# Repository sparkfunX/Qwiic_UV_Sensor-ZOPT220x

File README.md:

Qwiic UV Sensor - ZZOPT2201
========================================

[*SPX-14264*](https://www.sparkfun.com/products/14264)

The ZOPT2201 is an excellent UVBS (ultraviolet energy sensor) in that it does true 310nm UVB sensing, not interpolated UV from ambient light like most sensors on the market. Without fuss or weird look up tables this sensor gives the current UV Index accurately.

The [Qwiic system](http://www.sparkfun.com/qwiic) enables fast and solderless connection between popular platforms and various sensors and actuators. You can read more about the Qwiic system [here](http://www.sparkfun.com/qwiic). 

License Information
-------------------

This product is _**open source**_!

Please review the LICENSE.md file for license information.

If you have any questions or concerns on licensing, please contact techsupport@sparkfun.com.

Distributed as-is; no warranty is given.

- Your friends at SparkFun.

_<COLLABORATION CREDIT>_

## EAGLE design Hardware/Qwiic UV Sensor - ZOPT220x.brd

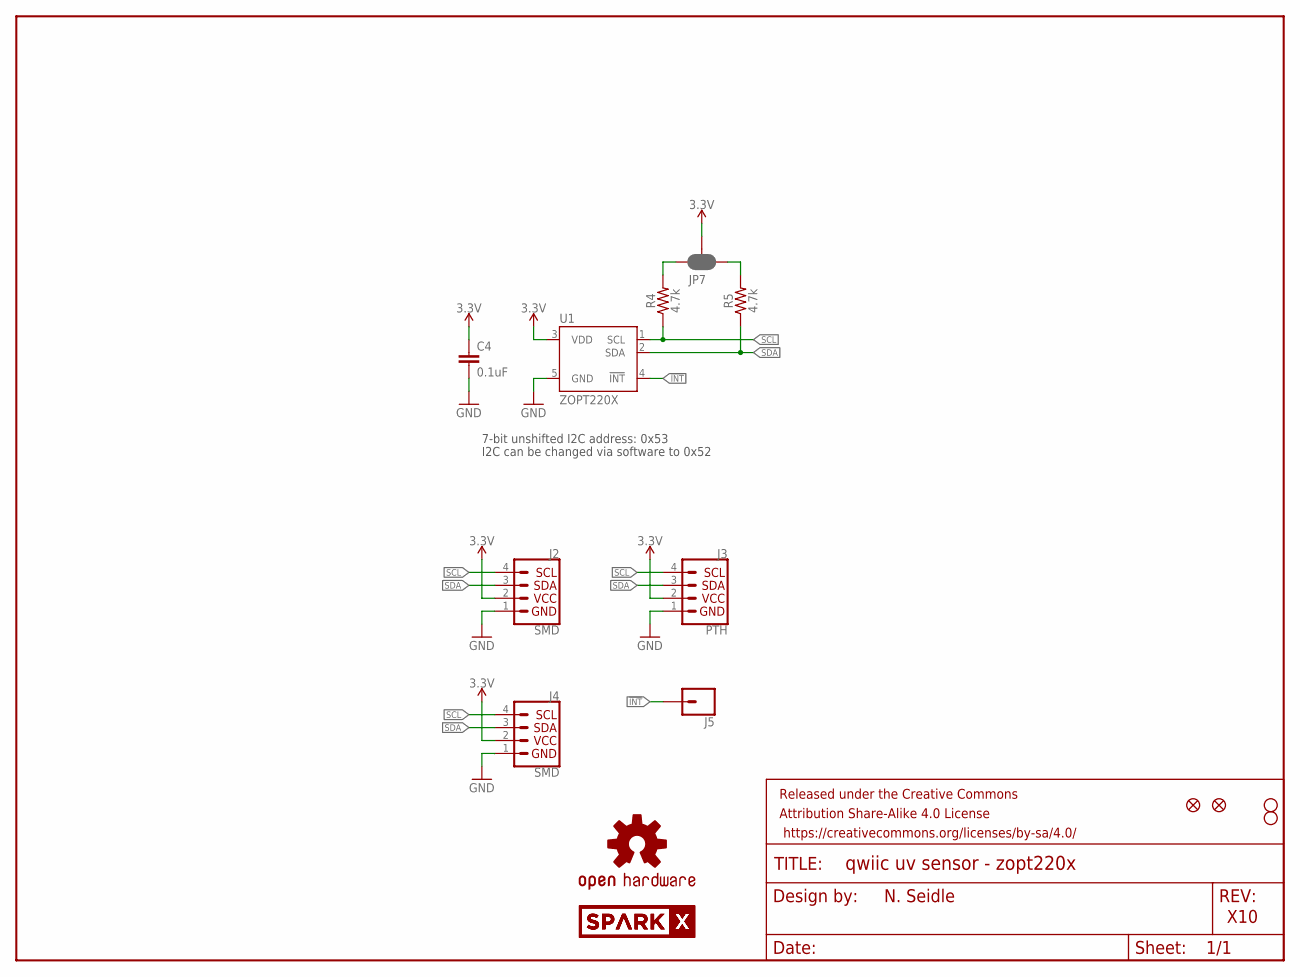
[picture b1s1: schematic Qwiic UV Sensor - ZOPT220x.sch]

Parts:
C4: 0.1uF; 0603
FRAME1: FRAME-LETTER; CREATIVE_COMMONS
J2, J4: SMD; 1X04_1MM_RA
J3: PTH; 1X04_NO_SILK
J5: CONN_01PTH_NO_SILK_YES_STOP; 1X01_NO_SILK
JP2, JP6: FIDUCIALUFIDUCIAL; MICRO-FIDUCIAL
JP3, JP4: STAND-OFF
JP7: JUMPER-SMT_3_2-NC_PASTE_SILK; SMT-JUMPER_3_2-NC_PASTE_SILK
LOGO1: OSHW-LOGOMINI; OSHW-LOGO-MINI
R4, R5: 4.7k; 0603
U1: ZOPT220X; LGA6
U$1, U$2: SPARKX-LOGO4; SPARKX-MEDIUM

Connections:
3.3V: C4.1, J2.2 (VCC), J3.2 (VCC), J4.2 (VCC), JP7.2, U1.3 (VDD)
!INT: J5.1, U1.4 (!INT)
GND: C4.2, J2.1 (GND), J3.1 (GND), J4.1 (GND), U1.5 (GND)
unnamed: JP7.1, R5.2
unnamed: JP7.3, R4.2
SCL: J2.4 (SCL), J3.4 (SCL), J4.4 (SCL), R4.1, U1.1 (SCL)
SDA: J2.3 (SDA), J3.3 (SDA), J4.3 (SDA), R5.1, U1.2 (SDA)

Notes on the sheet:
N. Seidle
X10
7-bit unshifted I2C address: 0x53
I2C can be changed via software to 0x52

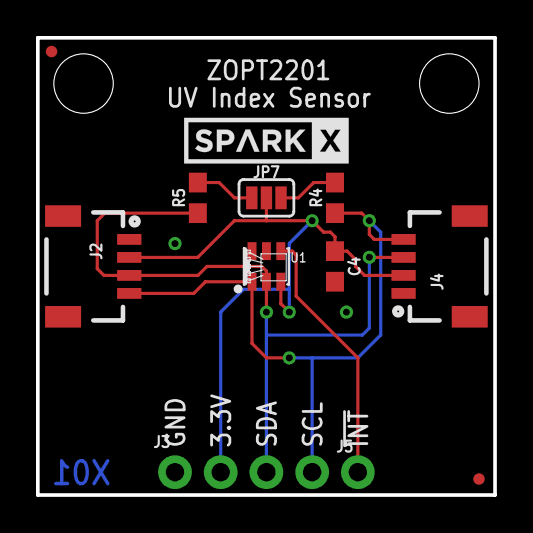
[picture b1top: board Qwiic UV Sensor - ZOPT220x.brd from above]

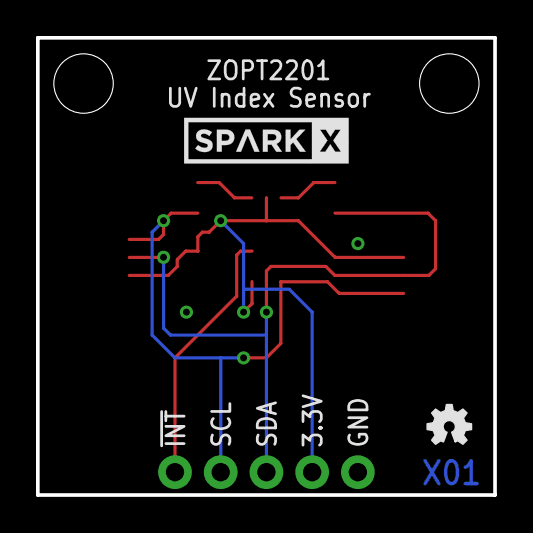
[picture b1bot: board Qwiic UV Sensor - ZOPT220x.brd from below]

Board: 2 copper layers, 25.4 x 25.4 mm, 17 parts (2 on the bottom side), 7 nets.

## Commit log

2017-03-10 :octocat: Added .gitattributes & .gitignore files
2017-04-07 Cleaning up file structure
2017-04-07 Adding examples. 6 is still work in progress.
2017-04-07 Adding Solar Elevation Angle Calculation

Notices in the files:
parts and their libraries:
SparkFun-Resistors: Licensing: Creative Commons ShareAlike 4.0 International - https://creativecommons.org/licenses/by-sa/4.0
SparkFun-Aesthetics: Released under the Creative Commons Attribution Share-Alike 4.0 License
SparkFun-Aesthetics: https://creativecommons.org/licenses/by-sa/4.0
